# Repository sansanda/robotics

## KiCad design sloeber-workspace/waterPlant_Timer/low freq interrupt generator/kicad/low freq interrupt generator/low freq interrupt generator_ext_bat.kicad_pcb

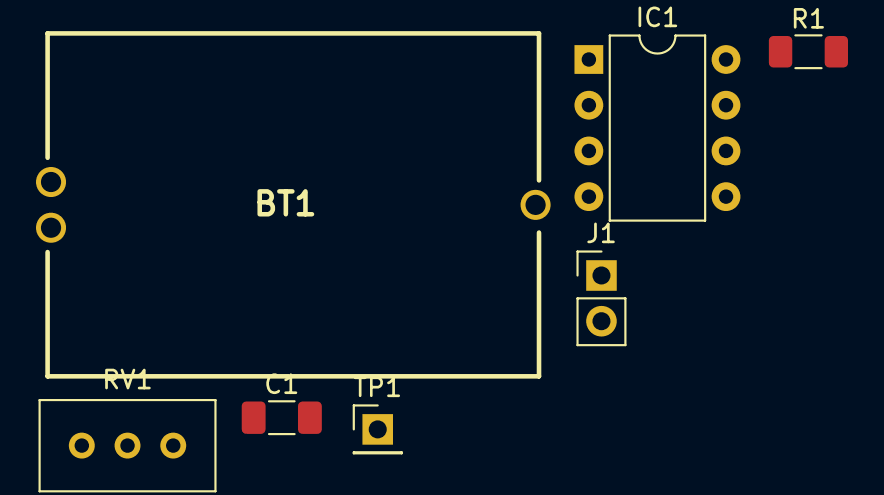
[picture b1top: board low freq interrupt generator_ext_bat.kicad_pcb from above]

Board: 2 copper layers, 7 parts (0 on the bottom side), 6 nets, no tracks yet.

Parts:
BT1: 120591-1; BatteryHolder_AmpTeConnectivity_CR2032_Horizontal_CircularH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
C1: 15uF; C_1206_3216Metric_Pad1.33x1.80mm_HandSolder
IC1: ICM7242IPAZ; DIP-8_W7.62mm
J1: Conn_01x02_Male; PinHeader_1x02_P2.54mm_Vertical
R1: 1M; R_1206_3216Metric_Pad1.30x1.75mm_HandSolder
RV1: 200K; Potentiometer_Bourns_3296W_Vertical
TP1: TestPoint; PinHeader_1x01_P2.54mm_Vertical

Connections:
unnamed: C1.2, IC1.7, RV1.2, RV1.3
unnamed: IC1.2, TP1.1
unnamed: IC1.3, J1.1
unnamed: R1.2, RV1.1
VDD: BT1.1, BT1.2, C1.1, IC1.1, IC1.6, R1.1
VSS: BT1.3, IC1.4, J1.2

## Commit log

2021-10-24 added folder ct6811
2021-10-24 added more files from ierobotics web
2021-10-24 added motors folder
2021-10-28 added test MPU6050 and waterPlant project
2021-11-12 testing adc
2021-11-12 testing adc2
2021-12-22 waterplant delay and water plat timer
2021-12-22 added claqueta projects
2022-01-10 waterplant_delay added display oled to show min-max and last moisture lecture
2022-01-10 removed waterplant timer1 folder
2022-01-10 new folder for waterplant timer
2022-01-11 waterplant timer: new folder for interrupt generator board, waterplant delay: solved non displaying values while taking care of plant
2022-01-11 waterplant_timer: created kicad pcb design for low freq interrupt generator
2022-01-12 1. pasamos a trabajar con arduino uno por problemas de estabilidad con el manejo de las interrupciones en nuestro nano. 2. waterplant_delay: rehecho el código mostrar mensajes por display y regar de 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
